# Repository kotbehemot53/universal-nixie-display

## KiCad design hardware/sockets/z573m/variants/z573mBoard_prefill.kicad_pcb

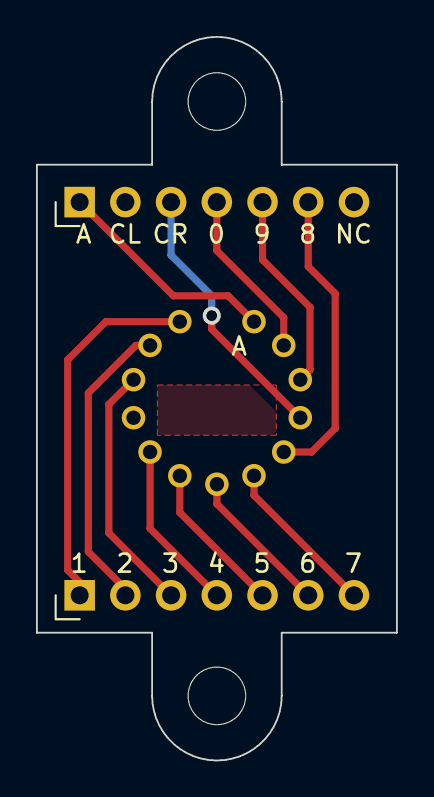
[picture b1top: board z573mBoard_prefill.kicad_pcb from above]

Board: 2 copper layers, 20.0 x 40.2 mm, 3 parts (0 on the bottom side), 12 nets.

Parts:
J1: Nixie Socket; Z570M
J2: Out Back; PinHeader_1x07_P2.54mm_Vertical
J3: Out Front; PinHeader_1x07_P2.54mm_Vertical

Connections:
unnamed: J1.1, J3.1
unnamed: J1.2, J3.2
unnamed: J1.3, J3.3
unnamed: J1.5 (4), J3.4
unnamed: J1.6 (5), J3.5
unnamed: J1.7 (6), J3.6
unnamed: J1.8 (7), J3.7
unnamed: J1.9 (8), J2.6 (8)
unnamed: J1.10 (CR), J2.3 (CR)
unnamed: J1.11 (9), J2.5 (9)
unnamed: J1.12 (0), J2.4 (0)
unnamed: J1.13 (A), J2.1 (A)

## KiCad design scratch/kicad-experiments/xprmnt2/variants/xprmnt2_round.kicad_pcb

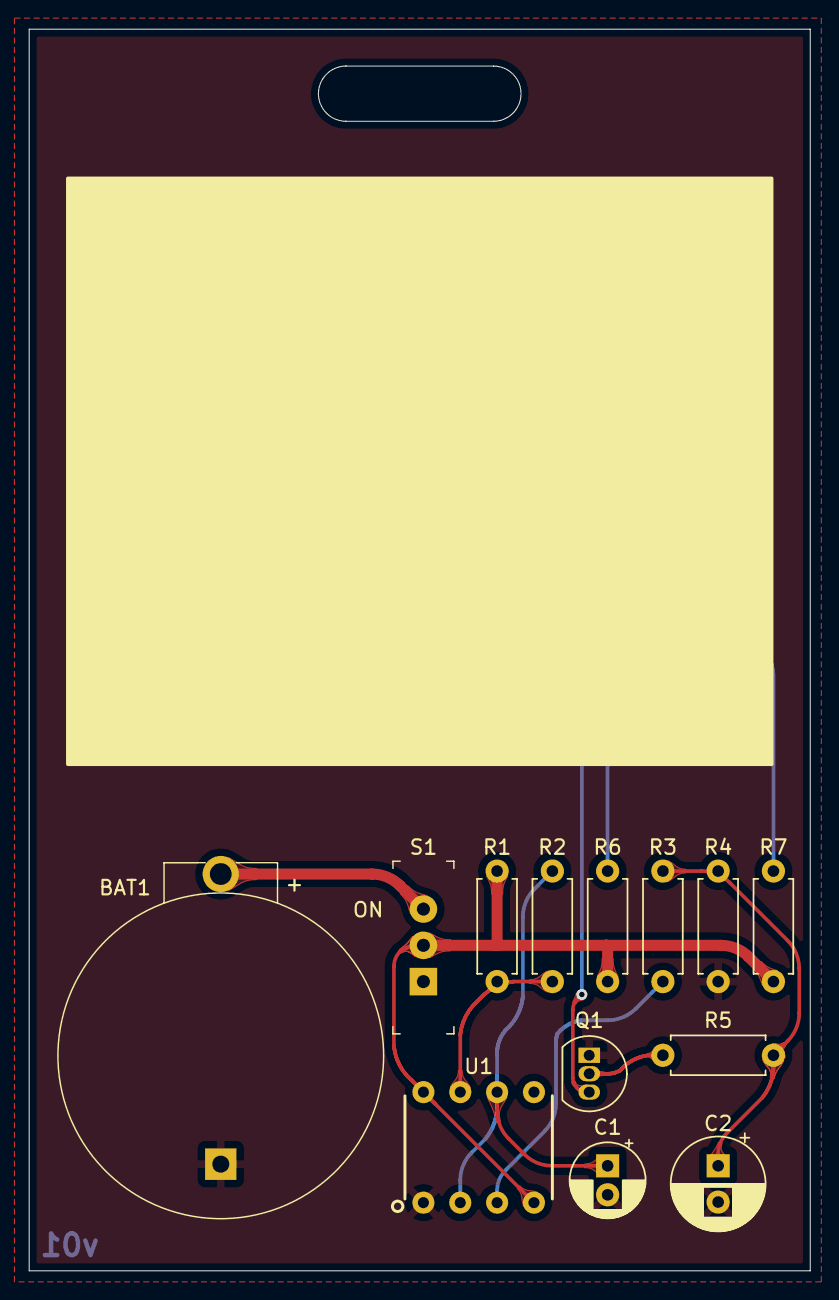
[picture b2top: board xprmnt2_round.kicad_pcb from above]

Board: 2 copper layers, 53.8 x 85.6 mm, 15 parts (0 on the bottom side), 11 nets.

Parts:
BAT1: BS-7; Battery_Holder_Coin_2032_BS-7
C1: 10uF; CP_Radial_D5.0mm_P2.00mm
C2: 100uF; CP_Radial_D6.3mm_P2.50mm
D1, D2: RED; LED_D3.0mm
Q1: 2N3904; TO-92_Inline
R1, R3: 22k; R_Axial_DIN0207_L6.3mm_D2.5mm_P7.62mm_Horizontal
R2: 330k; R_Axial_DIN0207_L6.3mm_D2.5mm_P7.62mm_Horizontal
R4: 100k; R_Axial_DIN0207_L6.3mm_D2.5mm_P7.62mm_Horizontal
R5: 10k; R_Axial_DIN0207_L6.3mm_D2.5mm_P7.62mm_Horizontal
R6, R7: 100; R_Axial_DIN0207_L6.3mm_D2.5mm_P7.62mm_Horizontal
S1: EG1218; Switch_Slide_11.6x4mm_EG1218
U1: 7555; ICM7555-PDIP

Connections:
GND: BAT1.Neg, C1.2, C2.2, Q1.1 (E), R4.2, U1.1 (GND)
unnamed: BAT1.Pos, S1.3
unnamed: C1.1, R2.2, U1.2 (~TRIG), U1.6 (THRESH)
unnamed: C2.1, R3.2, R4.1, R5.1
unnamed: D1.1 (K), D2.1 (K), Q1.3 (C)
unnamed: D1.2 (A), R6.2
unnamed: D2.2 (A), R7.2
unnamed: Q1.2 (B), R5.2
unnamed: R1.2, R2.1, U1.7 (DIS)
unnamed: R3.1, U1.3 (OUT)
VCC: R1.1, R6.1, R7.1, S1.2, U1.4 (~RST), U1.8 (VDD)

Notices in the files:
scratch/kicad-experiments/xprmnt2/variants/xprmnt2_round.kicad_pcb:
creativecommons.org/licenses/by/4.0
License: CC BY 4.0
